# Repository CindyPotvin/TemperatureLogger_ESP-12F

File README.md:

# TemperatureLogger_ESP-12F
Temperature logging PCB in KiCad based on ESP8266 (ESP-12F)

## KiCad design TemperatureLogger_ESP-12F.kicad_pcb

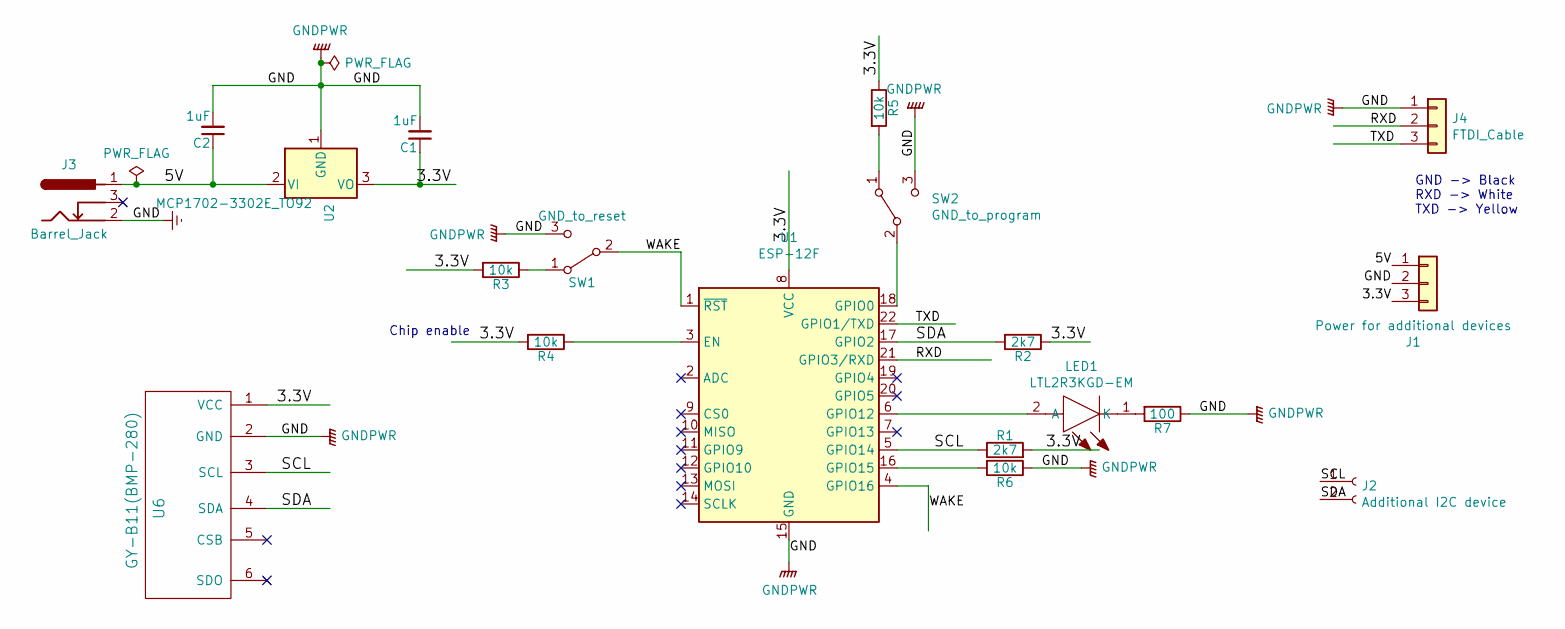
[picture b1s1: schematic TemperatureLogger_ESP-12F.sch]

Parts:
C1, C2: 1uF; FG18X7R1H334KRT00
J1: Power for additional devices; PinHeader_1x03_P2.54mm_Vertical
J2: Additional I2C device; PinHeader_1x02_P2.54mm_Vertical
J3: Barrel_Jack; PinHeader_1x02_P2.54mm_Vertical
J4: FTDI_Cable; PinHeader_1x03_P2.54mm_Vertical
LED1: LTL2R3KGD-EM; LTL2R3KGDEM; Mouser Part Number 859-LTL2R3KGD-EM
R1, R2: 2k7; R_Axial_DIN0204_L3.6mm_D1.6mm_P2.54mm_Vertical
R3, R4, R5, R6: 10k; R_Axial_DIN0207_L6.3mm_D2.5mm_P2.54mm_Vertical
R7: 100; R_Axial_DIN0204_L3.6mm_D1.6mm_P2.54mm_Vertical
SW1: GND_to_reset; B3F-1000
SW2: GND_to_program; EG1218
U1: ESP-12F; ESP-12E
U2: MCP1702-3302E_TO92; TO-92_Inline
U6: GY-B11(BMP-280); PinHeader_1x04_P2.54mm_Vertical

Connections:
/3.3V: C1.1, J1.3, R1.2, R2.1, R3.2, R4.2, R5.1, U1.8 (VCC), U2.3 (VO), U6.1 (VCC)
/5V: C2.1, J1.1, J3.1, U2.2 (VI)
/RXD: J4.2, U1.21 (GPIO3/RXD)
/SCL: J2.1, R1.1, U1.5 (GPIO14), U6.3 (SCL)
/SDA: J2.2, R2.2, U1.17 (GPIO2), U6.4 (SDA)
/TXD: J4.3, U1.22 (GPIO1/TXD)
/WAKE: SW1.2 (B), U1.1 (~RST), U1.4 (GPIO16)
Earth: C1.2, C2.2, J1.2, J3.2, J4.1, R6.1, R7.1, SW1.3 (C), SW2.3 (C), U1.15 (GND), U2.1 (GND), U6.2 (GND)
unnamed: LED1.1 (K), R7.2
unnamed: LED1.2 (A), U1.6 (GPIO12)
unnamed: R3.1, SW1.1 (A)
unnamed: R4.1, U1.3 (EN)
unnamed: R5.2, SW2.1 (A)
unnamed: R6.2, U1.16 (GPIO15)
unnamed: SW2.2 (B), U1.18 (GPIO0)

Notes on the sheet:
Chip enable
GND -> Black RXD -> White TXD -> Yellow

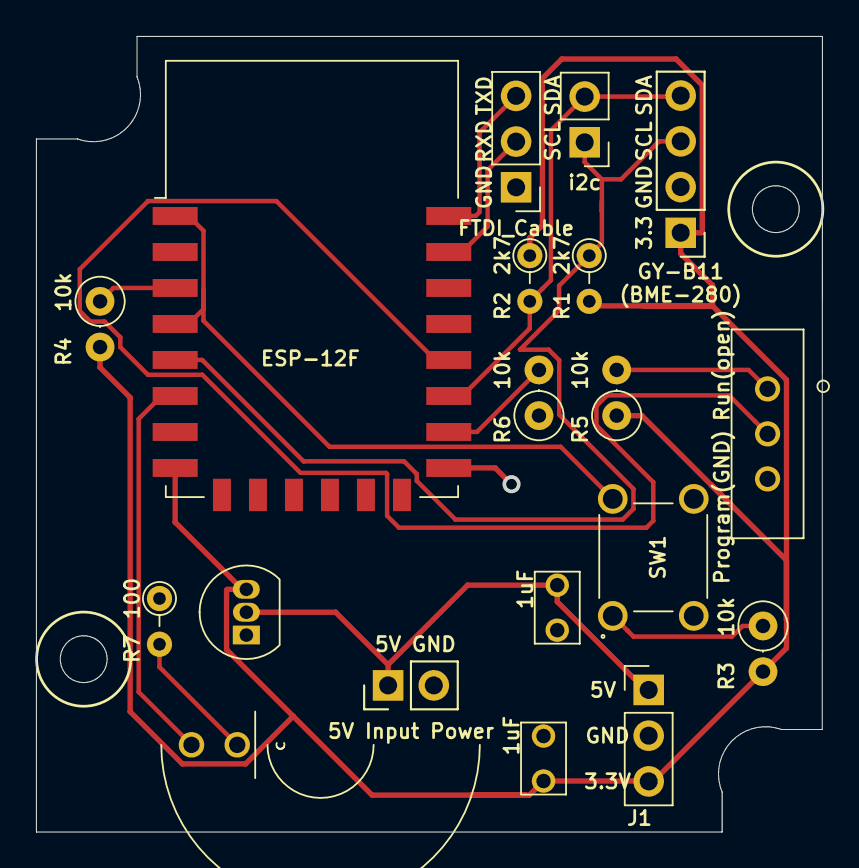
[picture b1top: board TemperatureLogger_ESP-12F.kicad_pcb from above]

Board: 2 copper layers, 43.7 x 44.2 mm, 19 parts (0 on the bottom side), 15 nets.

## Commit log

2019-07-07 PCB sent to production for the temperature logging modules in Kicad
2019-07-20 Adjusted BMP-280 footprint that was pointing to the wrong library
2019-11-23 Fixing the programming switch and starting to change the DC jack to fit in the box (component still too high)
2019-12-01 New revisions with headers for power and external sensor
2019-12-02 Changing the linear regulator to the right one on the schematic to be able to use 9V batteries
2020-02-16 Correcting SDA to use GPIO14 instead of pin 14 of ESP8266
